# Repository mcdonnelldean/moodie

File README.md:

# Moodie
Moodie is an a suite of hardware and software that enables you to add LED lighting around your home, office, or garden. It makes use of cheap and easy-to-source components, simple-to-solder Printed Circuit Boards as well as robust but easy to use software.

## Getting Started
If you simply wish to read about the project or otherwise do not intend to build any part of the project, you can view the documentation, online, at: 

- [moodie.mcddv.me]

[logo-img]: img/logo-pos.svg
[docs]:contributing/
[moodie.mcddv.me]: https://moodie.mcddv.me

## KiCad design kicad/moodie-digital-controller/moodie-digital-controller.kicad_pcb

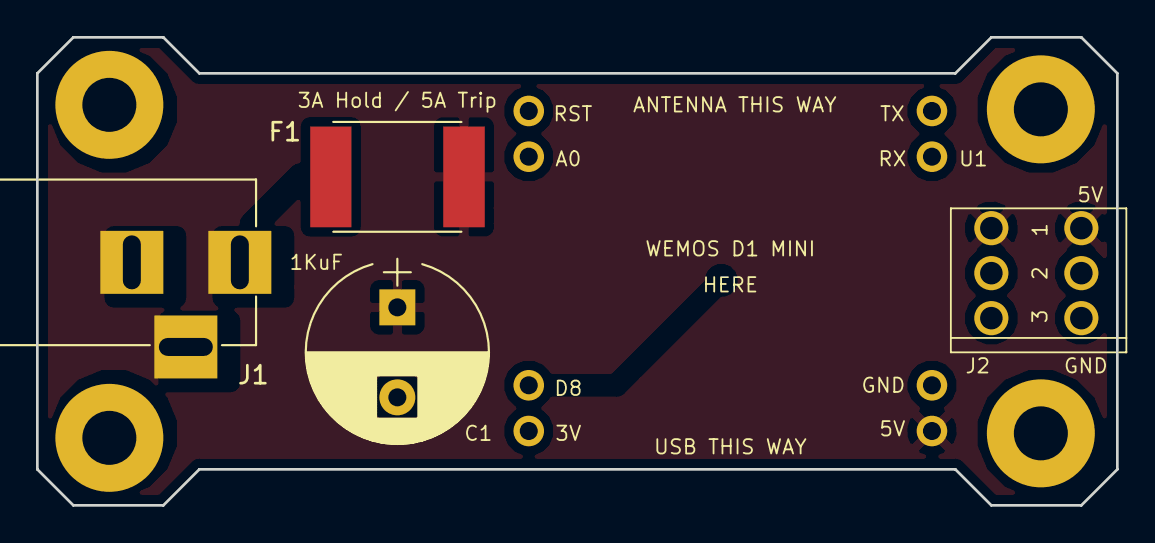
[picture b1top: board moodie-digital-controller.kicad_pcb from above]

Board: 2 copper layers, 60.0 x 26.0 mm, 5 parts (0 on the bottom side), 4 nets.

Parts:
C1: 1KuF; CP_Radial_D10.0mm_P5.00mm
F1: 3A Hold / 5A Trip; Fuse_SMD2920
J1: Barrel_Jack; BARREL_JACK
J2: Conn_01x03_Female; Spring_Conn_3Pin
U1: WEMOS_D1_MINI; WeMos_D1_Mini_Minimal_Connector

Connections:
+5V: C1.1, F1.1, J2.1, U1.16
/D8: J2.2, U1.7
GND: C1.2, J1.2, J1.3, J2.3, U1.15
unnamed: F1.2, J1.1

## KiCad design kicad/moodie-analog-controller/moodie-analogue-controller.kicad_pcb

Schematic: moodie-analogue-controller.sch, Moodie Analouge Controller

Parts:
J1: Barrel_Jack; BARREL_JACK
J2: RGB OUT; Spring_Conn_4Pin
Q1, Q2, Q3: IRLB8721; TO-220-3_Horizontal
U1: WEMOS_D1_MINI; WeMos_D1_Mini_Minimal_Connector

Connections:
+12V: J1.1, J2.1, U1.16
/BLUE: J2.4, Q3.2 (D)
/D1: Q1.1 (G)
/D2: Q2.1 (G)
/D3: Q3.1 (G)
/GREEN: J2.2, Q1.2 (D)
/RED: J2.3, Q2.2 (D)
GND: J1.2, J1.3, Q1.3 (S), Q2.3 (S), Q3.3 (S), U1.15

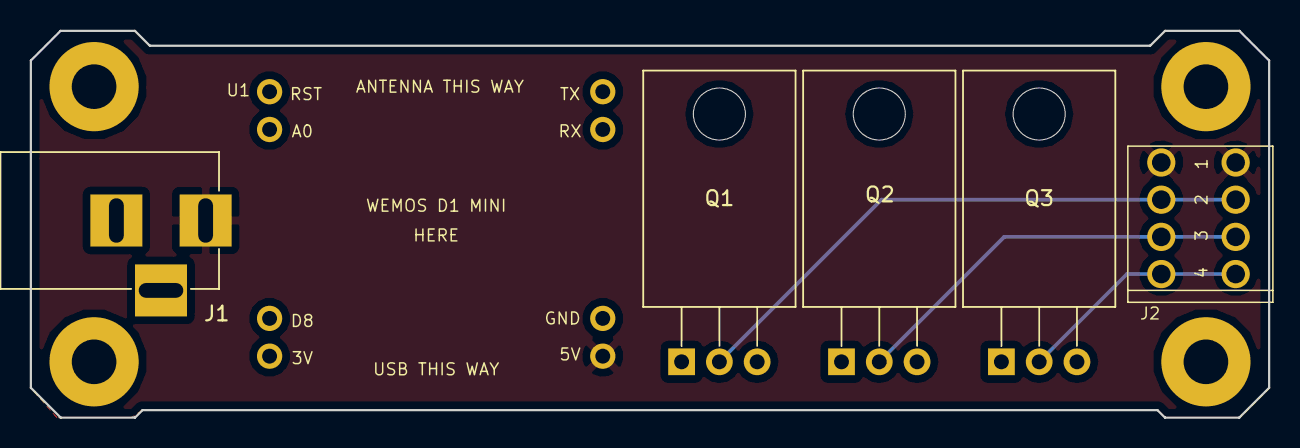
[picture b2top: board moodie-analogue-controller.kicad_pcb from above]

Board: 2 copper layers, 83.2 x 26.0 mm, 6 parts (0 on the bottom side), 5 nets.

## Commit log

2019-04-09 Create CNAME
2019-04-09 Analogueeeeeeeeeee
2019-04-09 Correct links, add git ignore
2019-04-10 Added initial fuse (it's too big)
2019-05-07 Fix link, remove DS_Store
2019-05-07 Tidyup (#1)
    * Added initial fuse (it's too big)
    * Fix link, remove DS_Store
2019-05-07 Make it https
2019-05-07 Make it https (#2)

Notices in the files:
kicad/moodie-analog-controller/moodie-analogue-controller.sch:
LICENSE: MIT
